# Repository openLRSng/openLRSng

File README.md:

openLRSng
=========

My fork of openLRS code (based on thUndeadMod of openLRS)

More information at http://openlrsng.org

CONFIGURATOR UTILITY / BINARY FIRMWARE NOTE:
============================================
  This software should be used in source form only by expert users, for normal use 'binary' firmwares can be uploaded and configured by free configuration software available for Windows/Mac/Linux from Chrome web store.

  http://goo.gl/iX7dJx

  Binary firmware images are also available from

  https://openlrsng.org/releases/

TRANSMITTER HW:
===============
  - TX_BOARD_TYPE 0 (Arduino Mini/nano 328 16MHz)
    - Flytron openLRS M1 (100mW) TX

  - TX_BOARD_TYPE 2 (Arduino Mini/nano 328 16MHz)
    - Flytron openLRS M2 (100mW)/M3(1W) TX
    - OrangeRX UHF TX unit

  - TX_BOARD_TYPE 3 (RX module acting as TX) (Arduino Mini/nano 328 16MHz)
    - Flytron openLRS RX v2
    - OrangeRX UHF RX
    - HawkEye openLRS RX

    - connect PPM input to 5th slot from left (channel 4)
    - button between ground and 4th slot from left (ch3)
    - buzzer via transistor on 3rd slot (ch2) (active high)

  - TX_BOARD_TYPE 4 (Arduino Mini/nano 328 16MHz)
    - openLRSngTX ('kha' or DIY based on ngTX schematics)
    - HawkEye OpenLRSng TX

  - TX_BOARD_TYPE 5 (RX as TX) (Arduino Mini/nano 328 16MHz)
    - DTFUHF/HawkEye 4ch/6ch RX

  - TX_BOARD_TYPE 6 (Arduino Leonardo)
    - DTFUHF/HawkEye deluxe TX

  - TX_BOARD_TYPE 7 (RX as TX)
    - Brotronics PowerTowerRX

  - RX_BOARD_TYPE 8 (RX as TX)
    - openLRSng microRX

RECEIVER HW:
============
  - RX_BOARD_TYPE 2 (TX module as RX) (328P 16MHz)

  - RX_BOARD_TYPE 3 (Arduino Mini/nano 328 16MHz)
    - Flytron openLRS RX
    - OrangeRX UHF RX (NOTE both LEDs are RED!!)
    - HawkEye OpenLRS RX

  - RX_BOARD_TYPE 5 (Arduino Mini/nano 328 16MHz)
    - DTFUHF/HawkEye 4ch/6ch RX

  - RX_BOARD_TYPE 7
    - Brotronics PowerTowerRX

  - RX_BOARD_TYPE 8
    - openLRSng microRX

  Receiver pin functiontions are mapped using the configurator or CLI interface.

SOFTWARE CONFIGURATION:
=======================
  Only hardware related selections are done in the openLRSng.ino (Arduino) or platformio.ini (VSCode/PlatformIO).

  Run time configuration is done by connecting to the TX module (which is put into binding mode) with serial terminal. For best restults use real terminal program like Putty, TeraTerm, minicom(Linux) but it is possible to use Arduino Serial Monitor too.
  Sending '<CR>' (enter) will enter the menu which will guide further. It should be noted that doing edits will automatically change 'RF magic' to force rebinding, if you want to use a specific magic set that using the command (and further automatic changes are ceased for the edit session).

  Datarates are: 0==4800bps 1==9600bps 2==19200bps 3==57600bps 4==125kbps

  Refer to http://openlrsng.org

UPLOADING:
==========
Use a 3v3 FTDI (or other USB to TTL serial adapter) and Arduino >= 1.0.

  o set board to "Arduino Pro or Pro Mini (5V, 16MHz) w/ atmega328" (yes it runs really on 3v3 but arduino does not need to know that)

  o define COMPILE_TX and upload to TX module

  o comment out COMPILE_TX and upload to RX

  o for deluxeTX "arduino boardtype" must be set to "Leonardo"

GENERATED FIRMWARE FILES:
=========================
Makefile generates TX/RX firmware files for each frequency 433/868/915 as well as all hardware types [RX/TX]-[#].hex.

The "*-bl.hex" files contain bootloader and can be used when flashing via ICSP.
  o 328p model (all but type 6) use optiboot bootloader and thus needs fuses set to: Low: FF High: DE Ext: 05.
  o type 6 uses 'caterina' and fuses should be set to: Low: FF High: D8 Ext: CB.

USERS GUIDE
===========

Please refer to http://openlrsng.org (->wiki)

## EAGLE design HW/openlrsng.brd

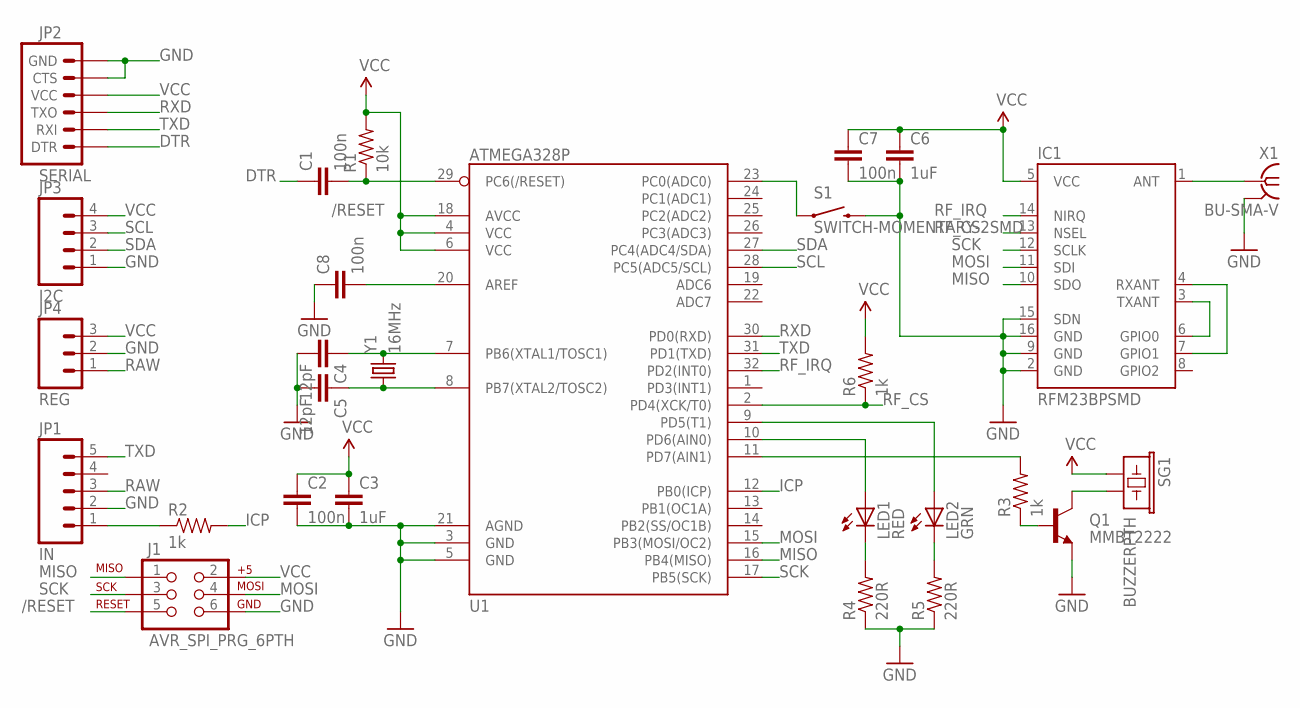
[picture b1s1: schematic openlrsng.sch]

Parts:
C1, C2, C7, C8: 100n; 0805
C3, C6: 1uF; 0805
C4, C5: 12pF; 0805
IC1: RFM23BPSMD; RFM23BP-S2
J1: AVR_SPI_PRG_6PTH; 2X3
JP1: IN; 1X05
JP2: SERIAL; 1X06
JP3: I2C; 1X04
JP4: REG; 1X03
LED1: RED; LED3MM
LED2: GRN; LED3MM
Q1: MMBT2222; SOT23-3
R1: 10k; 0402-RES
R2, R3, R6: 1k; 0402-RES
R4, R5: 220R; 0402-RES
S1: SWITCH-MOMENTARY-2SMD; TACTILE_SWITCH_SMD
SG1: BUZZERPTH; BUZZER-12MM
U1: ATMEGA328P; TQFP32-08
X1: BU-SMA-V
Y1: 16MHz; CRYSTAL-SMD-5X3

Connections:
/RESET: C1.2, J1.5, R1.1, U1.29 (PC6(/RESET))
DTR: C1.1, JP2.1 (DTR)
GND: C2.2, C3.2, C4.2, C5.2, C6.2, C7.2, C8.1, IC1.2 (GND), IC1.9 (GND), IC1.15 (SDN), IC1.16 (GND), J1.6, JP1.2, JP2.5 (CTS), JP2.6 (GND), JP3.1, JP4.2, Q1.2 (E), R4.1, R5.1, S1.3 (2), U1.3 (GND), U1.5 (GND), U1.21 (AGND), X1.2, X1.3 (2), X1.4 (2), X1.5 (2)
ICP: R2.2, U1.12 (PB0(ICP))
MISO: IC1.10 (SDO), J1.1, U1.16 (PB4(MISO))
MOSI: IC1.11 (SDI), J1.4, U1.15 (PB3(MOSI/OC2))
unnamed: IC1.3 (TXANT), IC1.6 (GPIO0)
unnamed: IC1.4 (RXANT), IC1.7 (GPIO1)
unnamed: JP1.1, R2.1
unnamed: R3.2, U1.11 (PD7(AIN1))
unnamed: Q1.1 (B), R3.1
unnamed: Q1.3 (C), SG1.- (2)
unnamed: LED1.A, U1.10 (PD6(AIN0))
unnamed: LED2.A, U1.9 (PD5(T1))
unnamed: LED1.K (C), R4.2
unnamed: LED2.K (C), R5.2
unnamed: C4.1, U1.7 (PB6(XTAL1/TOSC1)), Y1.3 (2)
unnamed: C5.1, U1.8 (PB7(XTAL2/TOSC2)), Y1.1
unnamed: IC1.1 (ANT), X1.1
unnamed: C8.2, U1.20 (AREF)
unnamed: S1.1, U1.23 (PC0(ADC0))
RAW: JP1.3, JP4.1
RF_CS: IC1.13 (NSEL), R6.1, U1.2 (PD4(XCK/T0))
RF_IRQ: IC1.14 (NIRQ), U1.32 (PD2(INT0))
RXD: JP2.3 (TXO), U1.30 (PD0(RXD))
SCK: IC1.12 (SCLK), J1.3, U1.17 (PB5(SCK))
SCL: JP3.3, U1.28 (PC5(ADC5/SCL))
SDA: JP3.2, U1.27 (PC4(ADC4/SDA))
TXD: JP1.5, JP2.2 (RXI), U1.31 (PD1(TXD))
VCC: C2.1, C3.1, C6.1, C7.1, IC1.5 (VCC), J1.2, JP2.4 (VCC), JP3.4, JP4.3, R1.2, R6.2, SG1.+ (1), U1.4 (VCC), U1.6 (VCC), U1.18 (AVCC)

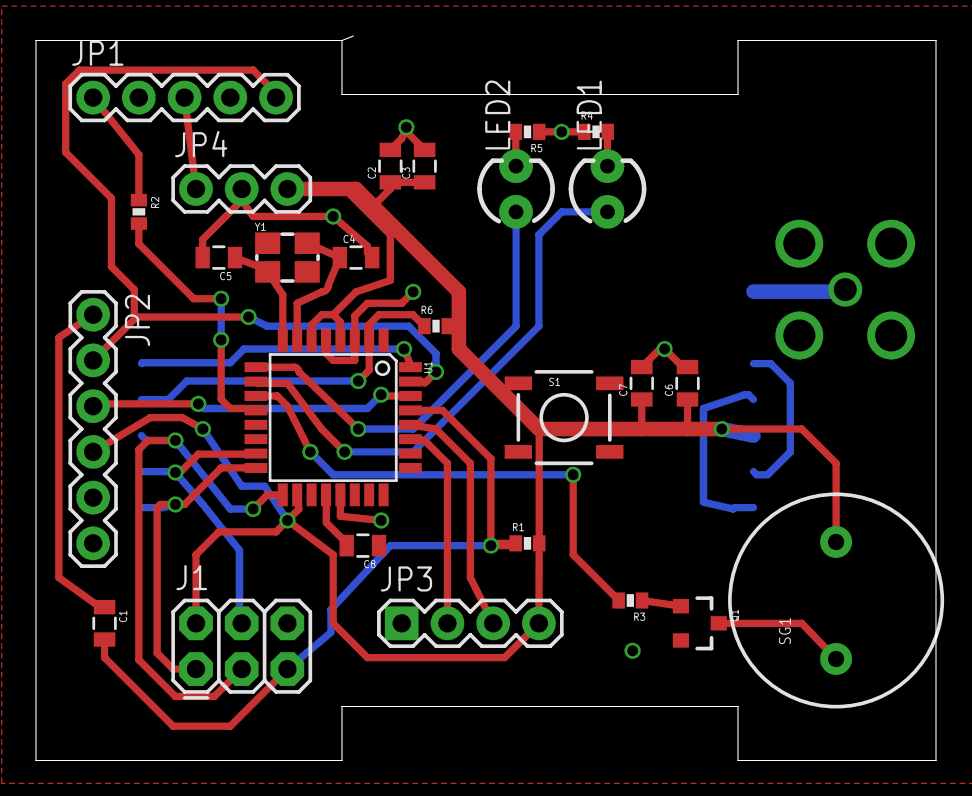
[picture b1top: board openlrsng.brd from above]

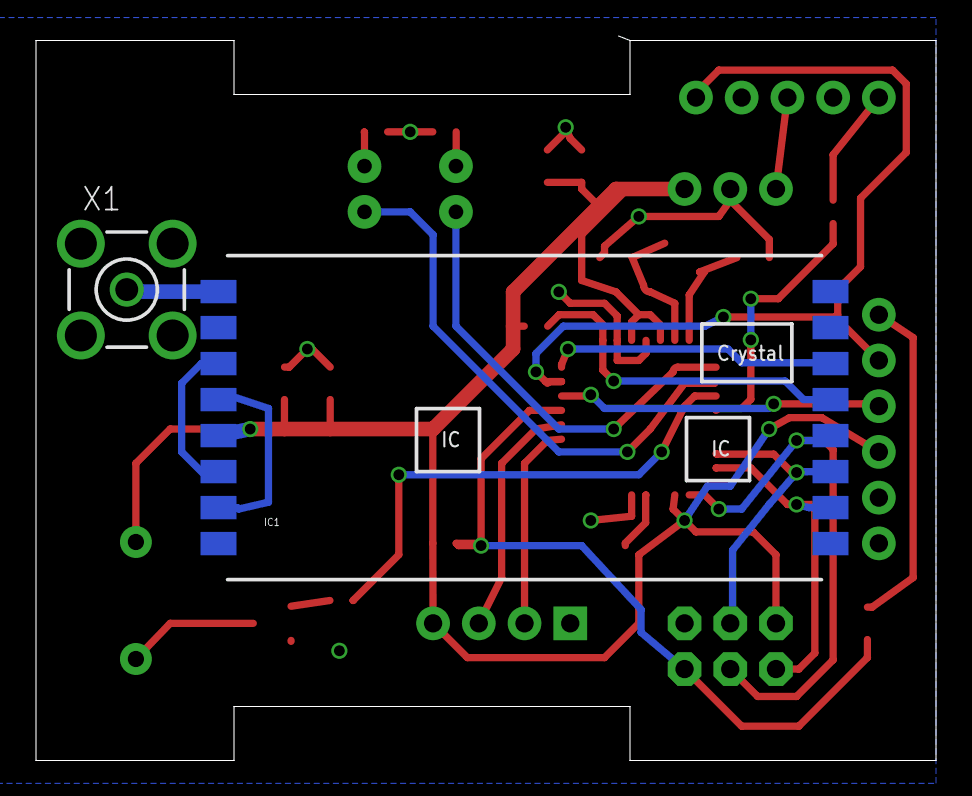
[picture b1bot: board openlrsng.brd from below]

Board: 2 copper layers, 50.0 x 40.0 mm, 28 parts (2 on the bottom side), 30 nets.

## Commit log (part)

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2013-08-19 Slave detection workking.
2013-08-22 Add 'LBEEP' code. This allows the RSSI pin to be used for audible beeps on packetloss via FPV audio link without any extra hardware.
2013-08-22 Spelling
2013-08-25 Configurator notices.
2013-09-01 boosting additional delay to 2 seconds
    also adding enter message for binary mode
2013-09-07 Move version to separate file
2013-09-07 PSP method to fetch firmware version number
2013-09-13 remove wire include
2013-10-03 PSP_REQ_SCANNER_MODE now sends ACK before enter
2013-10-03 Bumping version to 3.2.1
2013-11-04 Defaults updated for 6ch
2013-11-04 style fix
2013-11-05 Little fix.
2013-11-17 Rename PSP function variable
2013-11-19 Fixing it up.
2013-11-19 remove SERIAL_BAUDRATE from RX too
2013-11-19 Detach failsafe/PWMstop/PPMstop timeouts.
2013-11-19 cleanup
2013-11-19 cleanup / bugfix
2013-11-19 fix 6ch defaults to match pin swap
2013-11-20 Add A2 sensor support
2013-11-20 Add define for TelemetrySerial, needed on DeluxeTX
2013-11-21 Fix smartPort RSSI value range. Fix failsafe copy (type clash)
2013-11-21 More merge trouble
2013-11-21 little typofix
2013-11-23 Encode RF channel number into RFmagic, this will prevent RX from syncing to wrong slot in hop sequence when channels are overlapping.
2013-11-23 Add RX/TX startup messages.
2013-11-24 function ordering
2013-11-25 Fix missing ;
2013-11-26 Fix telemetry on 4+4 (a stupid bug....)
2013-11-26 linkQuality...
2013-11-26 remove unneeded flag
2013-11-28 typo fix
2013-11-28 v3.3.1
2013-11-28 other place to fix...
2013-11-29 Fix possible loading of failsafes due to out-of-order time assignment
2013-11-30 start RSSI refactor
2013-11-30 typo
2013-11-30 fix ppm disable
2013-12-07 typo...
2013-12-08 Bumb to v3.4(.0)
2013-12-18 Profile support. Factory reset by keeping bind button down > 10s is now changed to be 'profile swap' i.e. alternate configuration is activated on the TX. Active config is indicated by number of beeps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
2013-12-19 initial support for profile switching in PSP
2013-12-19 Fix PSP profile changing
2013-12-22 Code style cleanup, no logic changes.
2013-12-30 revisit the RSSI implementation
    This changes the behaviour to make a clear difference between RSSI
    and link quality.
    Composite RSSI now shows RSSI when linkquality is perfect as output
    values of 80-100%.
    If quality is degraded the composite output will switch to pure
    quality as 0-75%.
2013-12-30 Makefile stuff
2013-12-31 Bumb to 3.5 due to profile selection.
2014-01-01 Remove astyle binary stuff (does not belong to src repo)
2014-01-02 Version to 3.5.1 with no code changes because of compile issues on official 3.5 binaries.
2014-01-04 Basic diversity RX code may even work, untested for now.
2014-01-19 Make 868/915 firmwares too
2014-01-19 quick fix
2014-01-21 Allow using compilers from system location, if they are not part of Arduino install (e.g. on Fedora)
2014-01-22 Implement slaveRX recovery after failure.
2014-01-22 v3.5.3 - add diversity support (EXPERIMENTAL)
2014-01-23 Enable seding of 14 channels on spektrumsat.
2014-01-27 Fix SBUS output scaling.
2014-01-27 Disable hex backup/restore to save space.
2014-01-31 Allow 'fake' baudrates.
2014-01-31 Fix parity to even on SBUS output
2014-02-03 Removing obsolete buildall.sh (this is done by Makefile)
2014-02-08 Add Graupner SUMD input (set serial_baudrate to 4). Force sane baudrate on RX if using the 'magic' ones.
2014-02-08 fix little bug in PPM validation
2014-02-09 Shaving a few more bytes
2014-02-10 Clearer LED bahaviour when in PSP (configurator), CLI and spektrum modes. In all of these both LEDS are lit.
2014-02-12 Fix SUMD input
2014-02-13 Fix SUMD byte order.
2014-02-14 Add SUMD to RX config.
2014-02-16 Fix LED bahaviour on scannerMode
2014-02-21 Fix LLIND and switched outputs
2014-03-12 Loosen up validation for spektrum satellite packet.
2014-03-12 PSP fixes for failsafe
2014-03-12 move save routine below tx reply to avoid delays
2014-03-16 Testing watchdog on RX
2014-03-16 RX: put 'lockup by channel' code inside ifdef HALT_RX_BY_CH2
2014-03-16 Add WATCHDOG_USED flag to rxconfig.
2014-03-18 Fix byteorder for failsafe
2014-03-18 Change WD to 8 seconds Remove forced delay on failsafe saving.
2014-03-20 Enable WD on 32u4 (deluxeTX)
2014-03-23 Fix Leonardo bootloader enter.
2014-03-26 more work on tx_config
2014-03-27 initialize tx_config.flags with 0x00
2014-03-27 add rfm_type to tx_config struct
2014-03-28 Clean up makefile output - hide output from library compile - hide commands Remove the unneeded array declarations from binary_com.h Fixup Serial.begin() warning on Leonardo
2014-04-04 frequency & max_frequency in bindRandomize
2014-04-05 adding optimized CRC-16 function to binding.h
2014-04-06 removing EEPROM_RX_OFFSET
2014-04-06 also get/set active profile
2014-04-06 moving stuff around to binding area
2014-04-06 adding new eeprom calls to RX as well
    failsafe is read/write is still missing
2014-04-06 initial hooks to new eeprom in failsafe functions
2014-04-07 Add 'PPM DUMP' debug code (ifdeffed)
2014-04-07 utils: add shell script for snooping serialport access (Linux)
2014-04-07 populate EEPROM duplicates, no recovery of failed blocks yet
2014-04-09 bugfix for addressBase and addressNeedle
2014-04-09 increasing wait delay for EEPROM write operations
2014-04-09 more delay
2014-04-09 Limit eeprom copies to 4
2014-04-09 removing obsolete code
2014-04-09 astyle
2014-04-10 transfer watchdog status on REQ TX CONFIG
2014-04-10 Makefile magic... reduces size a lot!
2014-04-10 Fix lockout on overflow of Telemetry buffer (TX side)
2014-04-17 TX: make bootup faster
2014-04-19 Reorganize flags and fix duplicate watchdog/microPPM flag
2014-04-20 Bumping it up to 3.6.2.
2014-04-22 Make configurator check time static 50ms even if PPM is present. This should be good compromise.
2014-05-07 Initial commit for PowerTowerRX target.
2014-05-07 Add PowerTower RX into dialog.
2014-05-20 send ppmAge along with PPM data
2014-05-22 Make use of the SDN pin on supported hardware; required for JRdTX due to long electrical startup time
2014-05-24 Less hardcoded commands
2014-05-26 Fix RXD/TXD as normal output.
2014-05-30 Accept 4 channel PPM (previously minimum was 6)
2014-05-31 Clean up copy-paste from Makefile
2014-05-31 Image with bootloader for 32u4 too.
2014-06-16 Enable configurable minimum channel count for PPM input.
2014-06-16 Just a little cleanup on da define.
2014-06-30 Preliminary 8MHz support.
2014-07-31 Fixup
2014-07-31 Set RSSI to zero on total linkfail
2014-08-18 Minimize time with interrupts disabled, this should solve issues with PPM glitching with OrangeRX/Flytron gear.
2014-08-27 Support for Flytron/OrangeRX TX as receiver, this is completely untested atm.
2014-08-30 Add 'static beacon' mode, emit single tone for 20s at full power in place of fading tune.
2014-09-14 Bug fix for operation with slave present. More clear LED behaviour with slave.
2014-09-21 Fix Flytron M1 pins
2014-10-10 Fix ppmChannels going to 17 when 16ch is used without RSSI injection.
2014-10-10 Add Flytron M1 TX
2014-10-14 Disable CLI on 32u4
2014-10-22 Compile 8MHz version for the microRX.
2014-10-28 Initial commit for BroversityRX pinmap
2014-10-30 First pieces of diversity mode
2014-12-01 Include info about fuses.
2014-12-04 Version 3.7.4
2014-12-08 Profile cleanup o new PSP:s for setting default profile. o add 'boost' switch support Signed-off-by: Kari Hautio <khautio@gmail.com>
2014-12-09 Profileswitching: generalize to work with just one TX_MODE input
2014-12-09 Version 3.8.0, this is due to incompatbility in failsafe EEPROM/PSP.
2015-01-02 Initial support for locking failsafes from modification by 'button save'.
2015-01-04 RX: Add support for triggering beacon sequence externally
    Code samples RSSI on beacon frequency during hops when in failsafe
    state. If RSSI exceeds average by more than 10dB beacon sequnce is
    fired after 1 second.
2015-01-19 Adaptive randomization should work now
    Rest of implementation added and enabled storing to eeprom. Some
    debug prints still present and should be removed after correct
    operation is confirmed.
2015-01-19 chpicker: ensure correct math by promoting types by hand
2015-01-30 TX: enabled use of mode switch as channel
2015-01-30 TX: reinitialize eeprom in case BIND_VERSION has changed.
2015-02-22 Telemetry throughput improvements
    - default telemetry packet size changed to 1+16 from 1+8
    - add BIGPACKET mode, changes packetsize to 1+32
2015-02-23 TX/RX: more balanced us <-> 10bit mapping
2015-03-18 Fix profile to defaut to '1'.
2015-03-19 Fix version to 3.8.2
2015-04-30 fix small typos
2015-06-09 Remove unused variable.
2015-06-09 Fix finder mode
2015-06-14 binarycom: fix loop count
2016-01-07 Telemetry: do not send frsky telemetry frames on linkloss
    Fixes #96
2016-02-01 Update board type list
2016-02-28 Bump version to 3.8.8
2016-06-01 Do not indent links (breaks linking)
2016-11-11 Added support for serial MULTI protocol (serialMode == 5).
    Make it build under Arduino 1.6.11.
    Switched protocol number to 0x1b for 'OPENLRS'.
    Changed Tx channel value calculation to use 'servoUs2Bits'. Thanks to @csurf for pointing this out.
    Added multiprotocol configuration support.
    Added profile selection.
    Added profile switching.
2016-11-11 Improved performance of rescaling operation.
2016-12-13 Fixes for PPM, PPM init delay.
2016-12-15 Fixed build problem.
2017-02-27 Reset beacon after relink
    Previously beacon was not fully disabled and the RX listened for
    beacon trigger briefly after first packet causing the second
    packet being lost as it missed the preamble (third was received OK).
2017-03-06 move static timeout math ops to setup() function
    move these math calc ops to setup function
2017-12-16 Removed include for unneeded library.
2018-01-05 extend watchdog timer for lost-model beacon
    Temporarily set watchdog to 4sec within beacon routine to avoid timing
    out & resetting the RX (for watchdog-enabled RX's)
    This commit fixes #146
2018-01-10 add TX module configuration baud rate setting
    this adds an additional baudrate setting to the tx_config, allowing for
    connecting to the CLI/Configurator with a user-selected baudrate
    (instead of hard-coded 115200 baud)
    This resolves issue #141
2018-01-11 Fixed PPM signal monitor.
2018-01-22 fix start-up timing issue for 32u4
    add a start-up delay to mimic standard bootloader in order to allow
    Configurator time to detect boot message
2018-01-26 Layout change to conform to Arduino IDE requirements
    -Renamed "src" dir to "openLRSng" and associated path references
    -Minor fix for leonardo description in PIO config
    -Key source directory off of platformio.ini config file for build scripts
    -Readme to root directory
2018-01-27 Fixed compiler warnings.
2018-01-28 Fixed `make` build for TX.
2018-01-31 Additional gitignores
    -PlatformIO support files
    -cmake support files
    -Visual Studio support files
    -MacOS support files
    -additional general ignores
    .
2018-02-05 minor clean-up of RFM, common, and RX code
2018-02-09 fix SBUS input scaling for TX (using FrSky scaling)
2018-04-07 fix broken RX outputs for remote config
2018-04-10 fix telemetry packet interval
    for some reason, I mistakenly changed the offset value for telemetry
    packets. This reverts it to the original value & fixes backward
    compatibility with previous firmware versions.

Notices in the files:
parts and their libraries:
SparkFun-DigitalIC: Licensing: CC v3.0 Share-Alike You are welcome to use this library for commercial purposes.
